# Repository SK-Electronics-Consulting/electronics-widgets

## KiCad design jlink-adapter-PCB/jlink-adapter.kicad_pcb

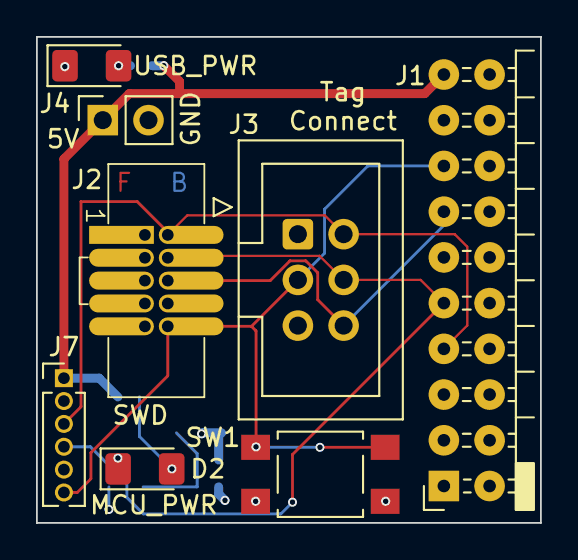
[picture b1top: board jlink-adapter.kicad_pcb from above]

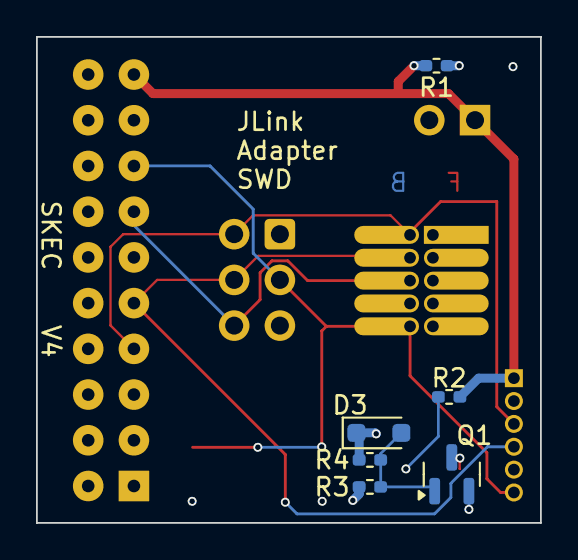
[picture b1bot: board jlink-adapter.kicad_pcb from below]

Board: 4 copper layers, 28.0 x 27.0 mm, 14 parts (6 on the bottom side), 11 nets.

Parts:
D1: Yellow; LED_1206_3216Metric_Pad1.42x1.75mm_HandSolder
D2: Red; LED_1206_3216Metric_Pad1.42x1.75mm_HandSolder
D3: D5V0L1B2WS-7; D_SOD-323_HandSoldering
J1: Conn_02x10_Odd_Even; PinSocket_2x10_P2.54mm_Horizontal_clipped_silkscreen
J2: Conn_02x05_Odd_Even; PinHeader_2x05_P1.27mm_Vertical_comb_SMT_TH
J3: Tag-Connect IDC; IDC-Header_2x03_P2.54mm_Vertical
J4: Conn_01x02; PinSocket_1x02_P2.54mm_Vertical
J7: Custom Segger Adapter; PinHeader_1x06_P1.27mm_Vertical
Q1: BSS123TA; SOT-23
R1, R2, R3: 1k; R_0402_1005Metric_Pad0.72x0.64mm_HandSolder
R4: 100k; R_0402_1005Metric_Pad0.72x0.64mm_HandSolder
SW1: SW_Push; SW_SPST_TL3305B

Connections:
+5V: J1.19, J4.1, J7.1, R1.1, R2.1
/RESET: J1.15, J2.10, J3.3 (~RESET), J7.6, SW1.1
/SWCLK: J1.9, J2.4, J3.4 (SWCLK), J7.4
/SWDIO: J1.7, J2.2, J3.2 (SWDIO), J7.3
/SWO: J1.13, J2.6, J3.6 (SWO)
/VTREF: J1.1, J2.1, J3.1 (VCC), J7.2, R3.1
GND: D1.1 (K), D3.1 (A1), J1.4, J1.6, J1.8, J1.10, J1.12, J2.3, J2.5, J2.9, J3.5 (GND), J4.2, J7.5, Q1.2 (S), R4.2, SW1.2
unnamed: D1.2 (A), R1.2
unnamed: D2.2 (A), R2.2
unnamed: D2.1 (K), Q1.3 (D)
unnamed: D3.2 (A2), Q1.1 (G), R3.2, R4.1
